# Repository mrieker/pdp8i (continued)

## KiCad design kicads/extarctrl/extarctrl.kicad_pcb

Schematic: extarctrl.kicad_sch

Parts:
C11, C12, C13, C14, C21, C22, C23, C24, C25, C26, C31, C32, C33, C34, C35, C36, C41, C42, C43, C44, C45, C46, C51, C52, C53, C54, C55, C61, C62, C63, C64, C65, C71, C72, C73, C74, C75, C81, C82, C83, C84: C; R_Axial_DIN0207_L6.3mm_D2.5mm_P7.62mm_Horizontal
E11, E21, E31, E41, E51, E71, E81: 74AHC540; DIP-20_W7.62mm
E12, E61: 74AC10
E13: 74AHC86; DIP-14_W7.62mm
E14, E23, E25, E26, E36, E44, E46, E53, E54, E63, E83: 74AHC00; DIP-14_W7.62mm
E22, E32, E42: 74HC85; DIP-16_W7.62mm
E24, E43, E55: 74HC27; DIP-14_W7.62mm
E33, E52, E75: 74HC175; DIP-16_W7.62mm
E34: 74HC30
E35: 74AHC02; DIP-14_W7.62mm
E45, E74: 74AC10; DIP-14_W7.62mm
E62: 74AC11; DIP-14_W7.62mm
E64, E72: 74AHC04; DIP-14_W7.62mm
E65: 74HC30; DIP-14_W7.62mm
E73: 74AHC74; DIP-14_W7.62mm
E82: 74AHC08; DIP-14_W7.62mm
E84: 74AC20; DIP-14_W7.62mm
J1, J2, J3, J4: Conn_01x36; PinHeader_1x36_P2.54mm_Vertical
J5: Conn_02x05_Odd_Even; PinHeader_2x05_P2.54mm_Vertical
R1: 47K; R_Axial_DIN0207_L6.3mm_D2.5mm_P7.62mm_Horizontal

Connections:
/CONSCK: J4.35
/CONSDA: J4.34
/_ACCLEAR: J3.28
/_ACUM_0: J3.7
/_ACUM_1: J2.34
/_ACUM_2: J2.27
/_ACUM_3: J2.20
/_ACUM_4: J2.13
/_ACUM_5: J2.7
/_ACUM_6: J1.35
/_ACUM_7: J1.29
/_ACUM_8: J1.23
/_ACUM_9: J1.16
/_ACUM_10: J1.9
/_ACUM_11: J1.2
/_BRKCYC: J4.33
/_BRKRQST: J3.29
/_BRKWRM: J4.11
/_BUSINI: E71.2 (A0), J3.31
/_BWCOV: J3.32
/_CAINC: J4.12
/_CLOCK: E71.3 (A1), J4.6
/_CYCLE3: J4.13
/_INBUS_0: E51.7 (A5), J3.10
/_INBUS_1: E51.3 (A1), J3.3
/_INBUS_2: E41.7 (A5), J2.30
/_INBUS_3: E41.3 (A1), J2.23
/_INBUS_4: E31.7 (A5), J2.16
/_INBUS_5: E31.4 (A2), J2.10
/_INBUS_6: E21.9 (A7), J2.4
/_INBUS_7: J1.32
/_INBUS_8: E21.4 (A2), J1.26
/_INBUS_9: E11.9 (A7), J1.19
/_INBUS_10: E11.6 (A4), J1.12
/_INBUS_11: E11.3 (A1), J1.5
/_INTINH: J4.15
/_INTRQST: J4.16
/_ION: J3.30
/_IOP: J4.8
/_IOSKIP: J4.17
/_IREG_9: J1.22
/_IREG_10: J1.15
/_IREG_11: J1.8
/_LINK: J4.9
/_LNKTOG: J4.18
/_MAJST_0: E71.8 (A6), J4.22
/_MAJST_1: E71.7 (A5), J4.21
/_MAJST_2: E71.6 (A4), J4.20
/_MAJST_3: E71.5 (A3), J4.19
/_MBUF_0: E51.6 (A4), J3.9
/_MBUF_1: E51.2 (A0), J3.2
/_MBUF_2: E41.6 (A4), J2.29
/_MBUF_3: E41.2 (A0), J2.22
/_MBUF_4: E31.6 (A4), J2.15
/_MBUF_5: E31.3 (A1), J2.9
/_MBUF_6: E21.8 (A6), J2.3
/_MBUF_7: E21.6 (A4), J1.31
/_MBUF_8: E21.3 (A1), J1.25
/_MBUF_9: E11.8 (A6), J1.18
/_MBUF_10: E11.5 (A3), J1.11
/_MBUF_11: E11.2 (A0), J1.4
/_MQUO_0: E51.8 (A6), J3.11
/_MQUO_1: E51.4 (A2), J3.4
/_MQUO_2: E41.8 (A6), J2.31
/_MQUO_3: E41.4 (A2), J2.24
/_MQUO_4: E31.8 (A6), J2.17
/_MQUO_5: E31.5 (A3), J2.11
/_MQUO_6: E31.2 (A0), J2.5
/_MQUO_7: E21.7 (A5), J1.33
/_MQUO_8: E21.5 (A3), J1.27
/_MQUO_9: E21.2 (A0), J1.20
/_MQUO_10: E11.7 (A5), J1.13
/_MQUO_11: E11.4 (A2), J1.6
/_PAUSE: E71.16 (Y2), J4.14
/_RESET: J4.7
/_RUN: J4.10
/_SCTR_0: E51.9 (A7), J3.13
/_SCTR_1: E51.5 (A3), J3.6
/_SCTR_2: E41.9 (A7), J2.33
/_SCTR_3: E41.5 (A3), J2.26
/_SCTR_4: E31.9 (A7), J2.19
/_SWCONT: J4.2
/_SWDEPOS: J3.35
/_SWEXAM: J3.34
/_SWLDAD: J3.33
/_SWSINST: J4.5
/_SWSSTEP: J4.4
/_SWSTART: J4.3
/_TP1: E81.3 (A1), J4.27
/_TP2: E71.9 (A7), J4.28
/_TP3: J4.29
/_TP4: J4.30
/_TS1: J4.23
/_TS2: J4.24
/_TS3: E81.2 (A0), J4.25
/_TS4: J4.26
/_dviover: E73.5 (Q), E74.4
/_extar: E33.11 (~Q2)
/_extarex: E64.9, E65.8
/_extop_1: E52.3 (~Q0), E61.5, E62.13, E63.13, J3.21
/_extop_2: E52.6 (~Q1), E62.2, E63.12, J3.20
/_extop_3: E35.6, E52.11 (~Q2), E61.4, E61.13, J3.19
/_extop_4: E14.4, E14.12, E25.4, E25.10, E26.5, E36.1, E46.2, E46.4, E46.10, E46.12, E52.14 (~Q3), E53.2, E53.4
/_extop_5: E33.3 (~Q0)
/_extop_6: E33.6 (~Q1)
/_extop_dvi: E61.12, E72.13, J3.23
/_extop_muy: E61.6, E72.3, J3.22
/_majst_1: E63.9, E64.4
/_majst_2: E64.10, E65.5
/_majst_3: E64.12, E65.3
/_nmidone: E82.11, E83.5
/_s3clk: E74.13, E75.15 (Q3), J3.24, J5.9
/busini: E71.18 (Y0), E72.1
/clk2: E74.12, E75.4 (D0), J5.2
/clk4: E75.2 (Q0), E75.5 (D1), J5.4
/clk6: E75.7 (Q1), E75.12 (D2), J5.6
/clk8: E75.10 (Q2), J5.8
/clkp1: E63.5, J5.10, R1.1
/clksel: E75.13 (D3), J5.1, J5.3, J5.5, J5.7
/clock: E71.17 (Y1), E73.11 (C), E75.9 (Cp)
/countedshift: E35.4, E83.12
/dviover: E73.6 (~Q), J3.25
/extar: E33.10 (Q2), E65.1
/extarex: E62.11, E64.8, J3.26
/extop_1: E35.9, E52.2 (Q0), E61.1, J3.18
/extop_2: E35.8, E52.7 (Q1), E61.2, E61.3, J3.17
/extop_3: E52.10 (Q2), E62.1, J3.16
/extop_4: E52.15 (Q3), J3.15
/extop_5: E23.5, E33.2 (Q0), E44.5, E44.10, E54.4, E63.1
/extop_6: E14.10, E23.12, E25.1, E26.2, E26.9, E33.7 (Q1), E36.12, E44.1, E44.13, E53.12, E54.2, E54.10, E54.12
/extop_dvi: E72.12, E74.3
/extop_muy: E72.4, E83.1
/extop_nmi: E62.12, E83.4
/inbus_0: E23.9, E51.13 (Y5)
/inbus_1: E51.17 (Y1), E52.4 (D0)
/inbus_2: E41.13 (Y5), E52.5 (D1)
/inbus_3: E41.17 (Y1), E52.12 (D2)
/inbus_4: E31.13 (Y5), E52.13 (D3)
/inbus_5: E31.16 (Y2), E33.4 (D0)
/inbus_6: E21.11 (Y7), E33.5 (D1)
/inbus_8: E21.16 (Y2), E23.10
/inbus_9: E11.11 (Y7), E12.5
/inbus_10: E11.14 (Y4), E12.4
/inbus_11: E11.17 (Y1), E12.3
/majst_0: E62.4, E65.4, E71.12 (Y6)
/majst_000x: E55.6, E62.3, J3.27
/majst_1: E55.3, E64.3, E71.13 (Y5)
/majst_2: E55.5, E64.11, E71.14 (Y4)
/majst_3: E55.4, E64.13, E71.15 (Y3)
/memop: E63.10, E63.11
/mquo_0: E51.12 (Y6), E54.9, E55.13
/mquo_1: E51.16 (Y2), E54.13, E55.2
/mquo_2: E41.12 (Y6), E54.1, E55.1
/mquo_3: E41.16 (Y2), E43.4, E44.12
/mquo_4: E31.12 (Y6), E43.3, E44.2
/mquo_5: E31.15 (Y3), E43.5, E53.13
/mquo_6: E24.10, E26.10, E31.18 (Y0)
/mquo_7: E21.13 (Y5), E24.9, E36.13
/mquo_8: E21.15 (Y3), E24.11, E26.1
/mquo_9: E21.18 (Y0), E24.13, E25.2
/mquo_10: E11.13 (Y5), E23.13, E24.2
/mquo_11: E11.16 (Y2), E14.9, E24.1
/myac_0: E43.9, E53.5, J3.12
/myac_1: E43.10, E46.9, J3.5
/myac_2: E25.5, E43.11, J2.32
/myac_3: E43.1, E46.5, J2.25
/myac_4: E43.13, E46.1, J2.18
/myac_5: E43.2, E53.1, J2.12
/myac_6: E35.12, E36.2, J2.6
/myac_7: E35.11, E46.13, J1.34
/myac_8: E26.4, E35.3, J1.28
/myac_9: E25.9, E35.2, J1.21
/myac_10: E13.9, E14.5, J1.14
/myac_11: E13.10, E14.13, J1.7
/myacstep2_0: E42.10 (A0), E61.8, J3.8
/myacstep2_1: E42.12 (A1), E45.8, J2.35
/myacstep2_2: E12.8, E42.13 (A2), J2.28
/myacstep2_3: E42.15 (A3), E45.6, J2.21
/myacstep2_4: E32.10 (A0), E45.12, J2.14
/myacstep2_5: E32.12 (A1), E53.8, J2.8
/myacstep2_6: E32.13 (A2), E36.6, J2.2
/myacstep2_7: E32.15 (A3), E36.8, J1.30
/myacstep2_8: E22.10 (A0), E26.11, J1.24
/myacstep2_9: E22.12 (A1), E25.11, J1.17
/myacstep2_10: E22.13 (A2), E23.3, J1.10
/myacstep2_11: E14.3, E22.15 (A3), J1.3
/pause: E62.8, E63.4, E71.4 (A2), E74.1
/s3clk: E75.14 (~Q3)
/sctr_0: E51.11 (Y7), E63.2
/sctr_1: E51.15 (Y3), E54.5
/sctr_2: E23.4, E41.11 (Y7)
/sctr_3: E41.15 (Y3), E44.9
/sctr_4: E31.11 (Y7), E44.4
/sctr_5: E74.5, E83.2, E83.13, J3.14
/tp1: E62.5, E81.17 (Y1)
/tp2: E71.11 (Y7), E73.3 (C)
/ts3: E62.9, E81.18 (Y0)
/yreg_0: E42.9 (B0), E51.14 (Y4)
/yreg_1: E42.11 (B1), E51.18 (Y0)
/yreg_2: E41.14 (Y4), E42.14 (B2)
/yreg_3: E41.18 (Y0), E42.1 (B3)
/yreg_4: E31.14 (Y4), E32.9 (B0)
/yreg_5: E31.17 (Y1), E32.11 (B1)
/yreg_6: E21.12 (Y6), E32.14 (B2)
/yreg_7: E21.14 (Y4), E32.1 (B3)
/yreg_8: E21.17 (Y1), E22.9 (B0)
/yreg_9: E11.12 (Y6), E22.11 (B1)
/yreg_10: E11.15 (Y3), E22.14 (B2)
/yreg_11: E11.18 (Y0), E22.1 (B3)
GND: C11.2, C12.2, C13.2, C14.2, C21.2, C22.2, C23.2, C24.2, C25.2, C26.2, C31.2, C32.2, C33.2, C34.2, C35.2, C36.2, C41.2, C42.2, C43.2, C44.2, C45.2, C46.2, C51.2, C52.2, C53.2, C54.2, C55.2, C61.2, C62.2, C63.2, C64.2, C65.2, C71.2, C72.2, C73.2, C74.2, C75.2, C81.2, C82.2, C83.2, C84.2, E11.1 (G1), E11.10 (GND), E11.19 (G2), E12.1, E12.2, E12.7 (GND), E12.13, E13.1, E13.2, E13.4, E13.5, E13.7 (GND), E13.12, E13.13, E14.7 (GND), E21.1 (G1), E21.10 (GND), E21.19 (G2), E22.8 (GND), E23.7 (GND), E24.4, E24.7 (GND), E25.7 (GND), E26.7 (GND), E31.1 (G1), E31.10 (GND), E31.19 (G2), E32.8 (GND), E33.8 (GND), E33.13 (D3), E34.7 (GND), E35.7 (GND), E36.7 (GND), E41.1 (G1), E41.10 (GND), E41.19 (G2), E42.2 (Ia<b), E42.4 (Ia>b), E42.8 (GND), E43.7 (GND), E44.7 (GND), E45.7 (GND), E46.7 (GND), E51.1 (G1), E51.10 (GND), E51.19 (G2), E52.8 (GND), E53.7 (GND), E54.7 (GND), E55.7 (GND), E55.9, E55.10, E55.11, E61.7 (GND), E62.7 (GND), E63.7 (GND), E64.1, E64.5, E64.7 (GND), E65.7 (GND), E71.1 (G1), E71.10 (GND), E71.19 (G2), E72.5, E72.7 (GND), E72.9, E73.7 (GND), E74.7 (GND), E74.9, E74.10, E74.11, E75.8 (GND), E81.1 (G1), E81.4 (A2), E81.5 (A3), E81.6 (A4), E81.7 (A5), E81.8 (A6), E81.9 (A7), E81.10 (GND), E81.19 (G2), E82.1, E82.2, E82.4, E82.5, E82.7 (GND), E82.9, E82.10, E83.7 (GND), E83.9, E83.10, E84.7 (GND), E84.9, E84.10, E84.12, E84.13, J1.36, J2.36, J3.36, J4.36
unnamed: E34.5, E55.12
unnamed: E13.8, E72.11
unnamed: E26.8, E36.5
unnamed: E26.6, E26.12
unnamed: E26.3, E26.13
unnamed: E72.10, E82.13
unnamed: E36.3, E36.4
unnamed: E36.10, E36.11
unnamed: E63.6, E73.12 (D)
unnamed: E73.8 (~Q), E74.2
unnamed: E14.1, E14.11
unnamed: E14.2, E14.8
unnamed: E14.6, E23.1
unnamed: E12.11, E25.6
unnamed: E25.8, E25.12
unnamed: E25.3, E25.13
unnamed: E12.9, E54.3
unnamed: E45.10, E54.6
unnamed: E54.8, E61.10
unnamed: E45.9, E54.11
unnamed: E12.10, E23.6
unnamed: E23.8, E24.5
unnamed: E23.2, E23.11
unnamed: E61.9, E63.3
unnamed: E63.8, E65.6
unnamed: E74.6, E84.1
unnamed: E83.3, E84.2
unnamed: E83.11, E84.4
unnamed: E83.6, E84.5
unnamed: E62.10, E84.6
unnamed: E53.3, E53.9
unnamed: E53.6, E61.11
unnamed: E53.10, E53.11
unnamed: E33.9 (Cp), E52.9 (Cp), E62.6
unnamed: E24.6, E33.12 (D2)
unnamed: E33.1 (~Mr), E52.1 (~Mr), E72.2
unnamed: E12.6, E24.3
unnamed: E34.12, E35.1
unnamed: E35.5, E35.10
unnamed: E34.11, E35.13
unnamed: E45.13, E46.3
unnamed: E45.4, E46.6
unnamed: E45.11, E46.8
unnamed: E36.9, E46.11
unnamed: E24.8, E34.2
unnamed: E24.12, E34.1
unnamed: E34.3, E43.6
unnamed: E34.6, E43.8
unnamed: E34.4, E43.12
unnamed: E44.3, E45.1
unnamed: E44.6, E45.2
unnamed: E44.11, E45.3
unnamed: E44.8, E45.5
unnamed: E34.8, E82.12
unnamed: E32.2 (Ia<b), E42.7 (Oa<b)
unnamed: E32.3 (Ia=b), E42.6 (Oa=b)
unnamed: E32.4 (Ia>b), E42.5 (Oa>b)
unnamed: E22.2 (Ia<b), E32.7 (Oa<b)
unnamed: E22.3 (Ia=b), E32.6 (Oa=b)
unnamed: E22.4 (Ia>b), E32.5 (Oa>b)
unnamed: E22.7 (Oa<b), E73.2 (D)
VCC: C11.1, C12.1, C13.1, C14.1, C21.1, C22.1, C23.1, C24.1, C25.1, C26.1, C31.1, C32.1, C33.1, C34.1, C35.1, C36.1, C41.1, C42.1, C43.1, C44.1, C45.1, C46.1, C51.1, C52.1, C53.1, C54.1, C55.1, C61.1, C62.1, C63.1, C64.1, C65.1, C71.1, C72.1, C73.1, C74.1, C75.1, C81.1, C82.1, C83.1, C84.1, E11.20 (VCC), E12.14 (VCC), E13.14 (VCC), E14.14 (VCC), E21.20 (VCC), E22.16 (VCC), E23.14 (VCC), E24.14 (VCC), E25.14 (VCC), E26.14 (VCC), E31.20 (VCC), E32.16 (VCC), E33.16 (VCC), E34.14 (VCC), E35.14 (VCC), E36.14 (VCC), E41.20 (VCC), E42.3 (Ia=b), E42.16 (VCC), E43.14 (VCC), E44.14 (VCC), E45.14 (VCC), E46.14 (VCC), E51.20 (VCC), E52.16 (VCC), E53.14 (VCC), E54.14 (VCC), E55.14 (VCC), E61.14 (VCC), E62.14 (VCC), E63.14 (VCC), E64.14 (VCC), E65.2, E65.11, E65.12, E65.14 (VCC), E71.20 (VCC), E72.14 (VCC), E73.1 (~R), E73.4 (~S), E73.10 (~S), E73.13 (~R), E73.14 (VCC), E74.14 (VCC), E75.1 (~Mr), E75.16 (VCC), E81.20 (VCC), E82.14 (VCC), E83.14 (VCC), E84.14 (VCC), J1.1, J2.1, J3.1, J4.1, R1.2

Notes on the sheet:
doing execute cycle of extended arithmetic * in FETCH cycle if no memory operand * in EXEC cycle if has memory operand
dviover clocked at every TP2 but we only care about the one during EXEC cycle of DVI it must be valid in time to block the PAUSE during TS3 myacstep2 was valid since just after FETCH TP1 yreg (really MBUF) valid since just after EXEC TP1 ...so it has 3 clocks to soak through the comparators
pause processor at beginning of TS3 while doing step 3 resume when termination condition met
perform step 3 clocking while processor pausing at beginning of TS3 shift registers (AC,MQ) clock on posedge s3clk J5 jumper (@ CLOCK 10MHz): 1-2 : 100nS on; 100nS off (MUY 6.5uS) 3-4 : 200nS on; 200nS off (MUY 8.8uS) 5-6 : 300nS on; 300nS off (MUY 11.1uS) 7-8 : 400nS on; 400nS off (MUY 13.4uS) 9-1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
SHL,ASR,LSR
opcode clocked at TP1 during FETCH * extar = it is an extended arith opcode * memop = the opcode has memory operand
myacstep2 = value to clock into MYAC at TP2 for non-memory ops (NOP,NMI), clocked at FETCH TP2 for memory ops (SCL,MUY,DVI,SHL,ASR,LSR), clocked at EXEC TP2 'or' of the following: extop<4> = 0 : MYAC (ACUM from step 1) extop<5> = 1 : SCTR from prior instruction extop<6> = 1 : MQUO from prior instru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
has memory operand SCL,MUY,DVI,SHL,ASR,LSR
dviover = (myac >= yreg)

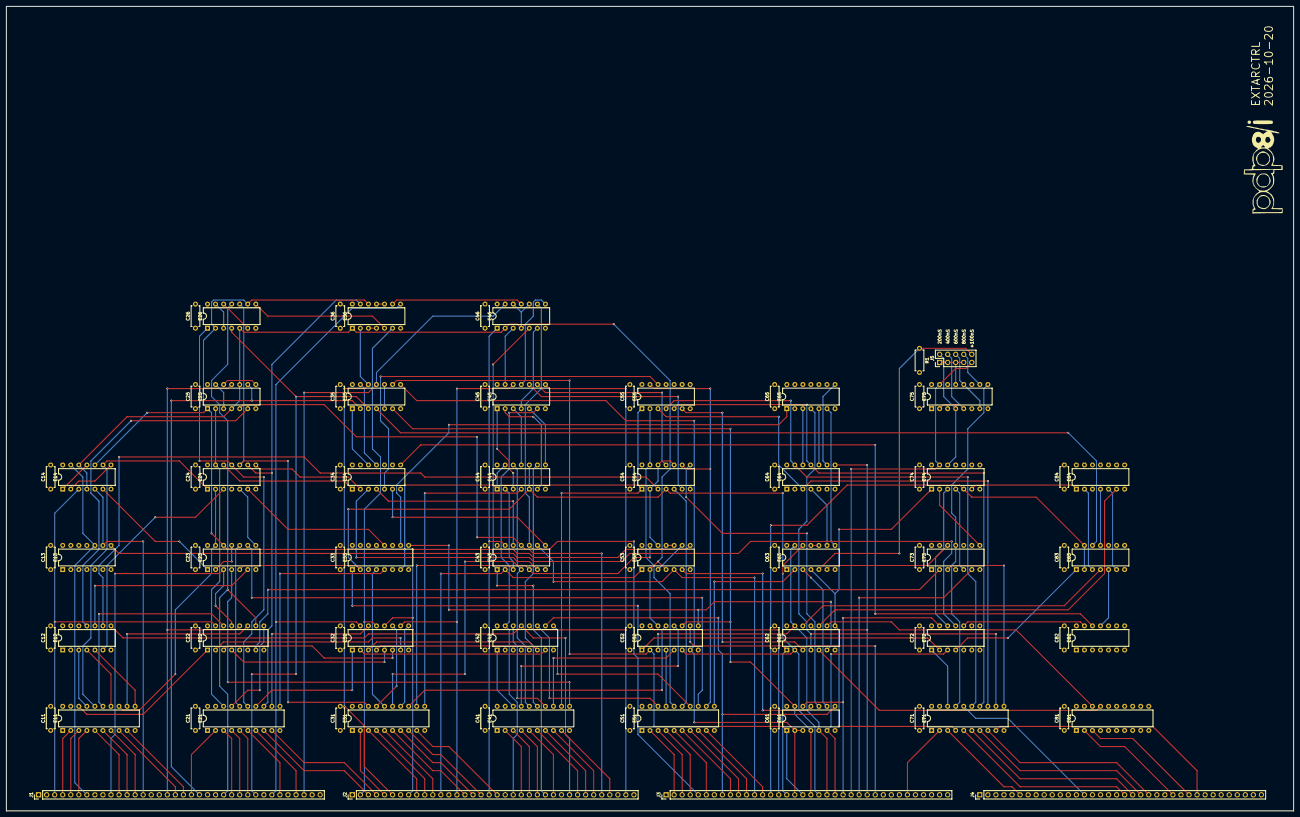
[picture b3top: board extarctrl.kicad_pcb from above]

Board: 4 copper layers, 406.4 x 254.0 mm, 88 parts (0 on the bottom side), 222 nets.

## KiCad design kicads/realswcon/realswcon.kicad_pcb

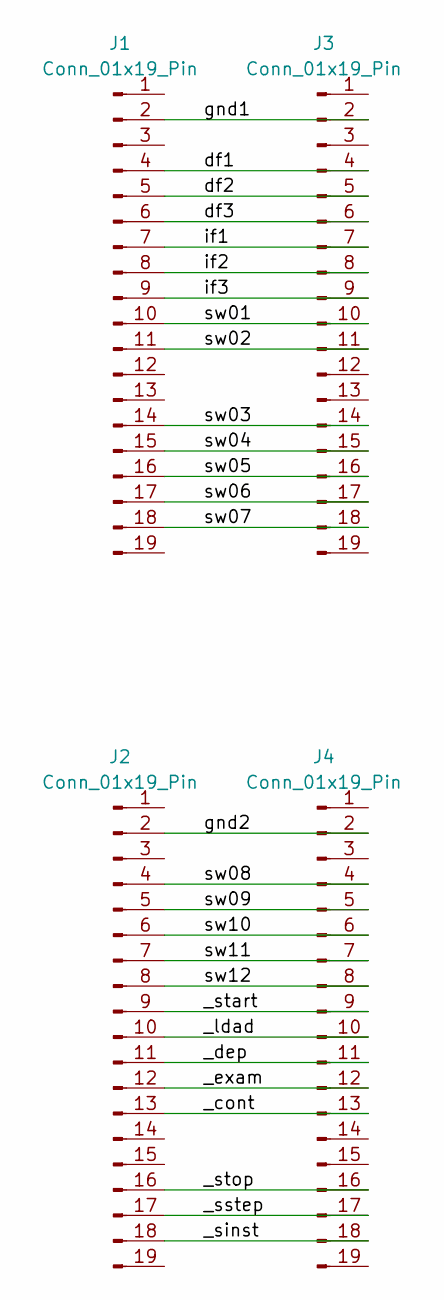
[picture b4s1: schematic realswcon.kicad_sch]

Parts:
J1, J2, J3, J4: Conn_01x19_Pin; PinHeader_1x19_P2.54mm_Vertical

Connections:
/_cont: J2.13, J4.13
/_dep: J2.11, J4.11
/_exam: J2.12, J4.12
/_ldad: J2.10, J4.10
/_sinst: J2.18, J4.18
/_sstep: J2.17, J4.17
/_start: J2.9, J4.9
/_stop: J2.16, J4.16
/df1: J1.4, J3.4
/df2: J1.5, J3.5
/df3: J1.6, J3.6
/gnd1: J1.2, J3.2
/gnd2: J2.2, J4.2
/if1: J1.7, J3.7
/if2: J1.8, J3.8
/if3: J1.9, J3.9
/sw01: J1.10, J3.10
/sw02: J1.11, J3.11
/sw03: J1.14, J3.14
/sw04: J1.15, J3.15
/sw05: J1.16, J3.16
/sw06: J1.17, J3.17
/sw07: J1.18, J3.18
/sw08: J2.4, J4.4
/sw09: J2.5, J4.5
/sw10: J2.6, J4.6
/sw11: J2.7, J4.7
/sw12: J2.8, J4.8

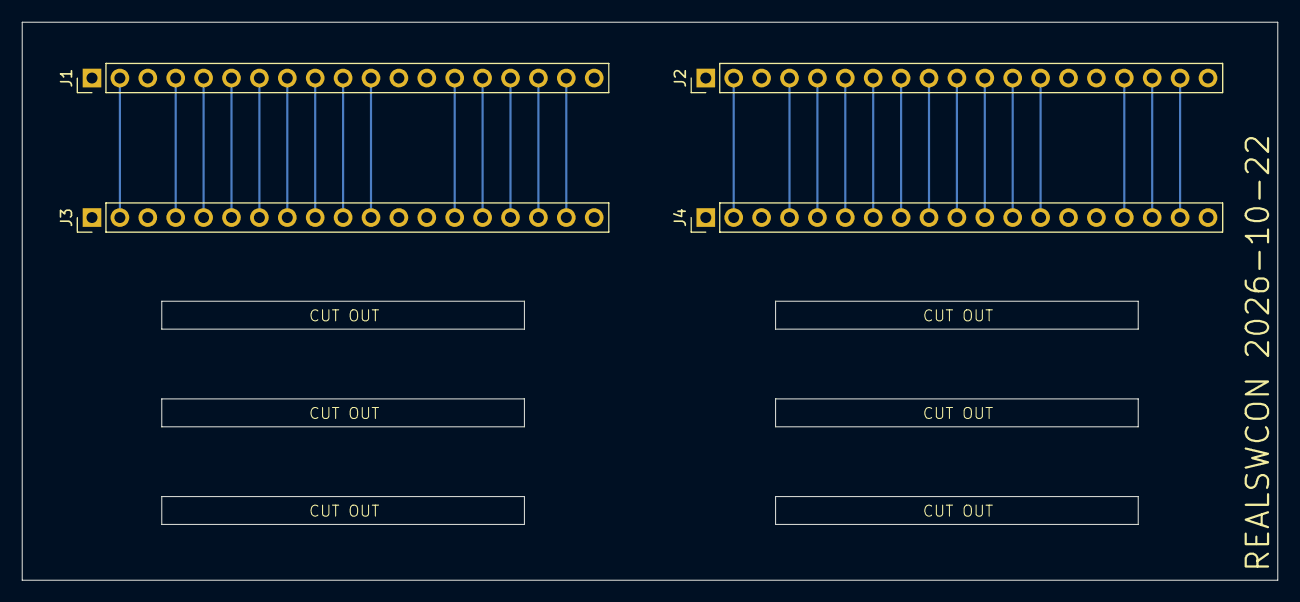
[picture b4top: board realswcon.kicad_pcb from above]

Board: 2 copper layers, 114.3 x 50.8 mm, 4 parts (0 on the bottom side), 28 nets.

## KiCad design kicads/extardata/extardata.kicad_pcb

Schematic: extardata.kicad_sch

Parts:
C11, C12, C13, C14, C15, C16, C17, C18, C21, C22, C23, C24, C25, C26, C27, C28, C31, C32, C33, C34, C35, C36, C37, C38, C41, C42, C43, C44, C45, C46, C47, C48, C51, C52, C53, C54, C55, C56, C57, C58, C61, C62, C63, C64, C65, C66, C67, C68, C71, C72, C73, C74, C75, C76, C77, C78, C81, C82, C83, C84, C85, C86, C87, C88: C; R_Axial_DIN0207_L6.3mm_D2.5mm_P7.62mm_Horizontal
E11, E21, E22, E31, E41, E51, E61, E81, E82: 74AHC540; DIP-20_W7.62mm
E12, E13, E17, E23, E24, E25, E27, E28, E33, E34, E35, E36, E37, E38, E42, E45, E48, E52, E56, E57, E58, E62, E63, E64, E65: 74AC151; DIP-16_W7.62mm
E14, E16, E32, E44, E53, E54: 74AC283; DIP-16_W7.62mm
E15, E43, E83: 74AHC04; DIP-14_W7.62mm
E18: 74AHC32; DIP-14_W7.62mm
E26, E46, E47, E55: 74AHC174; DIP-16_W7.62mm
E66, E68: 74AHC02; DIP-14_W7.62mm
E67: 74HC27; DIP-14_W7.62mm
E71, E72: 74AC161; DIP-16_W7.62mm
E73, E85: 74AHC157; DIP-16_W7.62mm
E74, E76, E77: 74AHC00; DIP-14_W7.62mm
E75, E78, E84: 74AC10; DIP-14_W7.62mm
E86: 74AC11; DIP-14_W7.62mm
E87: 74AHC08; DIP-14_W7.62mm
E88: 74AHC74; DIP-14_W7.62mm
J1, J2, J3, J4: Conn_01x36; PinHeader_1x36_P2.54mm_Vertical

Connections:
/CONSCK: J4.35
/CONSDA: J4.34
/_ACCLEAR: E41.14 (Y4), J3.28
/_ACUM_0: E61.8 (A6), J3.7
/_ACUM_1: E61.4 (A2), J2.34
/_ACUM_2: E51.8 (A6), J2.27
/_ACUM_3: E51.4 (A2), J2.20
/_ACUM_4: E31.8 (A6), J2.13
/_ACUM_5: E31.5 (A3), J2.7
/_ACUM_6: E31.2 (A0), J1.35
/_ACUM_7: E22.6 (A4), J1.29
/_ACUM_8: E22.3 (A1), J1.23
/_ACUM_9: E11.8 (A6), J1.16
/_ACUM_10: E11.5 (A3), J1.9
/_ACUM_11: E11.2 (A0), J1.2
/_BRKCYC: J4.33
/_BRKRQST: J3.29
/_BRKWRM: J4.11
/_BUSINI: E82.4 (A2), J3.31
/_BWCOV: J3.32
/_CAINC: J4.12
/_CLOCK: J4.6
/_CYCLE3: J4.13
/_INBUS_0: E41.15 (Y3), J3.10
/_INBUS_1: E41.16 (Y2), J3.3
/_INBUS_2: E41.17 (Y1), J2.30
/_INBUS_3: E41.18 (Y0), J2.23
/_INBUS_4: E21.11 (Y7), J2.16
/_INBUS_5: E21.12 (Y6), J2.10
/_INBUS_6: E21.13 (Y5), J2.4
/_INBUS_7: E21.14 (Y4), E22.8 (A6), J1.32
/_INBUS_8: E21.15 (Y3), J1.26
/_INBUS_9: E21.16 (Y2), J1.19
/_INBUS_10: E21.17 (Y1), J1.12
/_INBUS_11: E21.18 (Y0), J1.5
/_INTINH: J4.15
/_INTRQST: J4.16
/_ION: J3.30
/_IOP: J4.8
/_IOSKIP: E41.13 (Y5), J4.17
/_IREG_9: J1.22
/_IREG_10: J1.15
/_IREG_11: J1.8
/_LINK: E82.5 (A3), J4.9
/_LNKTOG: E41.11 (Y7), J4.18
/_MAJST_0: E82.6 (A4), J4.22
/_MAJST_1: J4.21
/_MAJST_2: J4.20
/_MAJST_3: J4.19
/_MBUF_0: E61.9 (A7), J3.9
/_MBUF_1: E61.5 (A3), J3.2
/_MBUF_2: E51.9 (A7), J2.29
/_MBUF_3: E51.5 (A3), J2.22
/_MBUF_4: E31.9 (A7), J2.15
/_MBUF_5: E31.6 (A4), J2.9
/_MBUF_6: E31.3 (A1), J2.3
/_MBUF_7: E22.7 (A5), J1.31
/_MBUF_8: E22.4 (A2), J1.25
/_MBUF_9: E11.9 (A7), J1.18
/_MBUF_10: E11.6 (A4), J1.11
/_MBUF_11: E11.3 (A1), J1.4
/_MQUO_0: E82.18 (Y0), J3.11
/_MQUO_1: E61.14 (Y4), J3.4
/_MQUO_2: E61.18 (Y0), J2.31
/_MQUO_3: E51.14 (Y4), J2.24
/_MQUO_4: E51.18 (Y0), J2.17
/_MQUO_5: E31.13 (Y5), J2.11
/_MQUO_6: E31.16 (Y2), J2.5
/_MQUO_7: E22.11 (Y7), J1.33
/_MQUO_8: E22.15 (Y3), J1.27
/_MQUO_9: E22.18 (Y0), J1.20
/_MQUO_10: E11.13 (Y5), J1.13
/_MQUO_11: E11.16 (Y2), J1.6
/_PAUSE: J4.14
/_RESET: J4.7
/_RUN: J4.10
/_SCTR_0: E82.17 (Y1), J3.13
/_SCTR_1: E61.13 (Y5), J3.6
/_SCTR_2: E61.17 (Y1), J2.33
/_SCTR_3: E51.13 (Y5), J2.26
/_SCTR_4: E51.17 (Y1), J2.19
/_SWCONT: J4.2
/_SWDEPOS: J3.35
/_SWEXAM: J3.34
/_SWLDAD: J3.33
/_SWSINST: J4.5
/_SWSSTEP: J4.4
/_SWSTART: J4.3
/_TP1: E81.2 (A0), J4.27
/_TP2: E81.3 (A1), J4.28
/_TP3: J4.29
/_TP4: J4.30
/_TS1: E82.7 (A5), J4.23
/_TS2: E82.8 (A6), J4.24
/_TS3: E82.9 (A7), J4.25
/_TS4: J4.26
/_busini: E46.1 (~Mr), E47.1 (~Mr), E71.1 (~MR), E72.1 (~MR), E83.4
/_enouts: E21.19 (G2), E41.19 (G2), E74.11
/_ensctrld: E71.9 (~PE), E72.9 (~PE), E84.8
/_extop_1: E84.2, E86.5, J3.21
/_extop_2: E84.13, E86.4, J3.20
/_extop_3: E74.2, E84.1, J3.19
/_extop_dvi: E68.3, J3.23
/_extop_muy: E66.3, J3.22
/_s3clk: E74.4, E75.11, E76.2, J3.24
/_ts2: E78.5, E78.13, E83.10
/_ts3: E66.6, E66.12, E67.2, E67.9, E76.4, E83.6
/_yreg_0: E54.6 (B1), E73.3 (I1a), E83.2
/_yreg_1: E43.6, E54.2 (B2), E73.6 (I1b)
/_yreg_2: E43.10, E54.15 (B3), E73.10 (I1c)
/_yreg_3: E43.8, E54.11 (B4), E73.13 (I1d)
/_yreg_4: E43.4, E44.6 (B1), E85.3 (I1a)
/_yreg_5: E43.2, E44.2 (B2)
/_yreg_6: E15.6, E44.15 (B3)
/_yreg_7: E43.12, E44.11 (B4)
/_yreg_8: E15.10, E16.6 (B1)
/_yreg_9: E15.2, E16.2 (B2)
/_yreg_10: E15.12, E16.15 (B3)
/_yreg_11: E15.8, E16.11 (B4)
/acclk: E26.9 (Cp), E55.9 (Cp), E75.8, E88.3 (C)
/acmux_0: E55.3 (D0), E63.5 (Z)
/acmux_1: E55.4 (D1), E62.5 (Z)
/acmux_2: E55.6 (D2), E64.5 (Z)
/acmux_3: E52.5 (Z), E55.11 (D3)
/acmux_4: E42.5 (Z), E55.13 (D4)
/acmux_5: E33.5 (Z), E55.14 (D5)
/acmux_6: E23.5 (Z), E26.3 (D0)
/acmux_7: E24.5 (Z), E26.4 (D1)
/acmux_8: E25.5 (Z), E26.6 (D2)
/acmux_9: E13.5 (Z), E26.11 (D3)
/acmux_10: E17.5 (Z), E26.13 (D4)
/acmux_11: E12.5 (Z), E26.14 (D5)
/acsel_0: E12.11 (S0), E13.11 (S0), E17.11 (S0), E23.11 (S0), E24.11 (S0), E25.11 (S0), E33.11 (S0), E42.11 (S0), E52.11 (S0), E62.11 (S0), E63.11 (S0), E64.11 (S0), E78.6
/acsel_1: E12.10 (S1), E13.10 (S1), E17.10 (S1), E23.10 (S1), E24.10 (S1), E25.10 (S1), E33.10 (S1), E42.10 (S1), E52.10 (S1), E62.10 (S1), E63.10 (S1), E64.10 (S1), E67.8
/acsel_2: E12.9 (S2), E13.9 (S2), E17.9 (S2), E23.9 (S2), E24.9 (S2), E25.9 (S2), E33.9 (S2), E42.9 (S2), E52.9 (S2), E62.9 (S2), E63.9 (S2), E64.9 (S2), E66.4
/acsel_zero: E12.7 (~E), E13.7 (~E), E17.7 (~E), E23.7 (~E), E24.7 (~E), E25.7 (~E), E33.7 (~E), E42.7 (~E), E52.7 (~E), E62.7 (~E), E63.7 (~E), E64.7 (~E), E87.3
/acum_0: E61.12 (Y6), E63.4 (I0)
/acum_1: E61.16 (Y2), E62.4 (I0)
/acum_2: E51.12 (Y6), E64.4 (I0)
/acum_3: E51.16 (Y2), E52.4 (I0)
/acum_4: E31.12 (Y6), E42.4 (I0)
/acum_5: E31.15 (Y3), E33.4 (I0)
/acum_6: E23.4 (I0), E31.18 (Y0)
/acum_7: E22.14 (Y4), E24.4 (I0)
/acum_8: E22.17 (Y1), E25.4 (I0)
/acum_9: E11.12 (Y6), E13.4 (I0)
/acum_10: E11.15 (Y3), E17.4 (I0)
/acum_11: E11.18 (Y0), E12.4 (I0)
/busini: E82.16 (Y2), E83.3
/clocksctr: E71.2 (CP), E72.2 (CP), E74.6
/dvi_shl: E67.1, E67.3, E67.10, E68.1
/dviacstep_0: E54.4 (S1), E63.1 (I3)
/dviacstep_1: E54.1 (S2), E62.1 (I3)
/dviacstep_2: E54.13 (S3), E64.1 (I3)
/dviacstep_3: E52.1 (I3), E54.10 (S4)
/dviacstep_4: E42.1 (I3), E44.4 (S1)
/dviacstep_5: E33.1 (I3), E44.1 (S2)
/dviacstep_6: E23.1 (I3), E44.13 (S3)
/dviacstep_7: E24.1 (I3), E44.10 (S4)
/dviacstep_8: E16.4 (S1), E25.1 (I3)
/dviacstep_9: E13.1 (I3), E16.1 (S2)
/dviacstep_10: E16.13 (S3), E17.1 (I3)
/dviacstep_11: E12.1 (I3), E16.10 (S4)
/dvicarry: E16.9 (C23), E18.5
/dviover: E65.1 (I3), J3.25
/dviqbit: E18.6, E37.1 (I3), E68.2
/extarex: E74.10, E74.12, E75.2, E84.10, J3.26
/extop_1: E65.11 (S0), E77.5, J3.18
/extop_2: E65.10 (S1), E66.8, E74.1, J3.17
/extop_3: E65.9 (S2), E67.4, E86.3, J3.16
/extop_4: E75.1, J3.15
/inbus_7: E22.12 (Y6), E87.1
/link: E65.3 (I1), E65.4 (I0), E76.5, E82.15 (Y3)
/majst_0: E82.14 (Y4), E84.5
/majst_000x: E84.3, J3.27
/mqclk: E46.9 (Cp), E47.9 (Cp), E76.3
/mqmux_0: E37.5 (Z), E47.3 (D0)
/mqmux_1: E47.4 (D1), E56.5 (Z)
/mqmux_2: E47.6 (D2), E57.5 (Z)
/mqmux_3: E47.11 (D3), E48.5 (Z)
/mqmux_4: E47.13 (D4), E58.5 (Z)
/mqmux_5: E28.5 (Z), E47.14 (D5)
/mqmux_6: E34.5 (Z), E46.3 (D0)
/mqmux_7: E36.5 (Z), E46.4 (D1)
/mqmux_8: E45.5 (Z), E46.6 (D2)
/mqmux_9: E35.5 (Z), E46.11 (D3)
/mqmux_10: E38.5 (Z), E46.13 (D4)
/mqmux_11: E27.5 (Z), E46.14 (D5)
/mqsel_0: E27.11 (S0), E28.11 (S0), E34.11 (S0), E35.11 (S0), E36.11 (S0), E37.11 (S0), E38.11 (S0), E45.11 (S0), E48.11 (S0), E56.11 (S0), E57.11 (S0), E58.11 (S0), E78.12
/mqsel_1: E27.10 (S1), E28.10 (S1), E34.10 (S1), E35.10 (S1), E36.10 (S1), E37.10 (S1), E38.10 (S1), E45.10 (S1), E48.10 (S1), E56.10 (S1), E57.10 (S1), E58.10 (S1), E67.12
/mqsel_2: E27.9 (S2), E28.9 (S2), E34.9 (S2), E35.9 (S2), E36.9 (S2), E37.9 (S2), E38.9 (S2), E45.9 (S2), E48.9 (S2), E56.9 (S2), E57.9 (S2), E58.9 (S2), E66.13
/mquo_0: E47.2 (Q0), E56.1 (I3), E56.14 (I5), E56.15 (I4), E66.2, E82.2 (A0)
/mquo_1: E37.2 (I2), E37.12 (I7), E37.13 (I6), E47.5 (Q1), E57.1 (I3), E57.14 (I5), E57.15 (I4), E61.6 (A4)
/mquo_2: E47.7 (Q2), E48.1 (I3), E48.14 (I5), E48.15 (I4), E56.2 (I2), E56.12 (I7), E56.13 (I6), E61.2 (A0)
/mquo_3: E47.10 (Q3), E51.6 (A4), E57.2 (I2), E57.12 (I7), E57.13 (I6), E58.1 (I3), E58.14 (I5), E58.15 (I4)
/mquo_4: E28.1 (I3), E28.14 (I5), E28.15 (I4), E47.12 (Q4), E48.2 (I2), E48.12 (I7), E48.13 (I6), E51.2 (A0)
/mquo_5: E31.7 (A5), E34.1 (I3), E34.14 (I5), E34.15 (I4), E47.15 (Q5), E58.2 (I2), E58.12 (I7), E58.13 (I6)
/mquo_6: E28.2 (I2), E28.12 (I7), E28.13 (I6), E31.4 (A2), E36.1 (I3), E36.14 (I5), E36.15 (I4), E46.2 (Q0)
/mquo_7: E22.9 (A7), E34.2 (I2), E34.12 (I7), E34.13 (I6), E45.1 (I3), E45.14 (I5), E45.15 (I4), E46.5 (Q1)
/mquo_8: E22.5 (A3), E35.1 (I3), E35.14 (I5), E35.15 (I4), E36.2 (I2), E36.12 (I7), E36.13 (I6), E46.7 (Q2)
/mquo_9: E22.2 (A0), E38.1 (I3), E38.14 (I5), E38.15 (I4), E45.2 (I2), E45.12 (I7), E45.13 (I6), E46.10 (Q3)
/mquo_10: E11.7 (A5), E27.1 (I3), E27.14 (I5), E27.15 (I4), E35.2 (I2), E35.12 (I7), E35.13 (I6), E46.12 (Q4)
/mquo_11: E11.4 (A2), E38.2 (I2), E38.12 (I7), E38.13 (I6), E46.15 (Q5), E54.5 (A1), E63.14 (I5), E63.15 (I4)
/muy_lsr: E66.1, E66.9, E67.5, E77.1
/muyacstep_0: E53.1 (S2), E63.2 (I2)
/muyacstep_1: E53.13 (S3), E62.2 (I2)
/muyacstep_2: E53.10 (S4), E64.2 (I2)
/muyacstep_3: E32.4 (S1), E52.2 (I2)
/muyacstep_4: E32.1 (S2), E42.2 (I2)
/muyacstep_5: E32.13 (S3), E33.2 (I2)
/muyacstep_6: E23.2 (I2), E32.10 (S4)
/muyacstep_7: E14.4 (S1), E24.2 (I2)
/muyacstep_8: E14.1 (S2), E25.2 (I2)
/muyacstep_9: E13.2 (I2), E14.13 (S3)
/muyacstep_10: E14.10 (S4), E17.2 (I2)
/muyacstep_11: E12.2 (I2), E14.9 (C23)
/muymqstep_11: E27.2 (I2), E53.4 (S1)
/myac_0: E27.12 (I7), E27.13 (I6), E37.3 (I1), E41.5 (A3), E53.5 (A1), E54.3 (A2), E55.2 (Q0), E62.14 (I5), E62.15 (I4), J3.12
/myac_1: E41.4 (A2), E53.3 (A2), E54.14 (A3), E55.5 (Q1), E56.3 (I1), E63.12 (I7), E63.13 (I6), E64.14 (I5), E64.15 (I4), J3.5
/myac_2: E41.3 (A1), E52.14 (I5), E52.15 (I4), E53.14 (A3), E54.12 (A4), E55.7 (Q2), E57.3 (I1), E62.12 (I7), E62.13 (I6), J2.32
/myac_3: E41.2 (A0), E42.14 (I5), E42.15 (I4), E44.5 (A1), E48.3 (I1), E53.12 (A4), E55.10 (Q3), E64.12 (I7), E64.13 (I6), J2.25
/myac_4: E21.9 (A7), E32.5 (A1), E33.14 (I5), E33.15 (I4), E44.3 (A2), E52.12 (I7), E52.13 (I6), E55.12 (Q4), E58.3 (I1), J2.18
/myac_5: E21.8 (A6), E23.14 (I5), E23.15 (I4), E28.3 (I1), E32.3 (A2), E42.12 (I7), E42.13 (I6), E44.14 (A3), E55.15 (Q5), J2.12
/myac_6: E21.7 (A5), E24.14 (I5), E24.15 (I4), E26.2 (Q0), E32.14 (A3), E33.12 (I7), E33.13 (I6), E34.3 (I1), E44.12 (A4), J2.6
/myac_7: E16.5 (A1), E21.6 (A4), E23.12 (I7), E23.13 (I6), E25.14 (I5), E25.15 (I4), E26.5 (Q1), E32.12 (A4), E36.3 (I1), J1.34
/myac_8: E13.14 (I5), E13.15 (I4), E14.5 (A1), E16.3 (A2), E21.5 (A3), E24.12 (I7), E24.13 (I6), E26.7 (Q2), E45.3 (I1), J1.28
/myac_9: E14.3 (A2), E16.14 (A3), E17.14 (I5), E17.15 (I4), E21.4 (A2), E25.12 (I7), E25.13 (I6), E26.10 (Q3), E35.3 (I1), J1.21
/myac_10: E12.14 (I5), E12.15 (I4), E13.12 (I7), E13.13 (I6), E14.14 (A3), E16.12 (A4), E21.3 (A1), E26.12 (Q4), E38.3 (I1), J1.14
/myac_11: E12.13 (I6), E14.12 (A4), E17.12 (I7), E17.13 (I6), E18.4, E21.2 (A0), E26.15 (Q5), E27.3 (I1), E65.13 (I6), E76.13, J1.7
/myacstep2_0: E63.3 (I1), J3.8
/myacstep2_1: E62.3 (I1), J2.35
/myacstep2_2: E64.3 (I1), J2.28
/myacstep2_3: E52.3 (I1), J2.21
/myacstep2_4: E42.3 (I1), J2.14
/myacstep2_5: E33.3 (I1), J2.8
/myacstep2_6: E23.3 (I1), J2.2
/myacstep2_7: E24.3 (I1), J1.30
/myacstep2_8: E25.3 (I1), J1.24
/myacstep2_9: E13.3 (I1), J1.17
/myacstep2_10: E17.3 (I1), J1.10
/myacstep2_11: E12.3 (I1), J1.3
/mylink: E41.9 (A7), E65.5 (Z)
/sctr_0: E72.14 (Q0), E82.3 (A1)
/sctr_1: E61.7 (A5), E72.13 (Q1)
/sctr_2: E61.3 (A1), E72.12 (Q2)
/sctr_3: E51.7 (A5), E72.11 (Q3)
/sctr_4: E51.3 (A1), E71.14 (Q0)
/sctr_5: E71.13 (Q1), J3.14
/shllink: E65.14 (I5), E65.15 (I4), E88.5 (Q)
/tp1: E81.18 (Y0), E84.4
/tp2: E74.9, E75.13, E81.17 (Y1), E83.13
/ts1: E82.13 (Y5), E87.2
/ts2: E82.12 (Y6), E83.11, E84.9
/ts3: E71.7 (CEP), E72.7 (CEP), E72.10 (CET), E74.13, E76.12, E77.2, E77.4, E82.11 (Y7), E83.5
/yreg_0: E53.6 (B1), E61.11 (Y7), E83.1
/yreg_1: E43.5, E53.2 (B2), E61.15 (Y3)
/yreg_2: E43.11, E51.11 (Y7), E53.15 (B3)
/yreg_3: E43.9, E51.15 (Y3), E53.11 (B4)
/yreg_4: E31.11 (Y7), E32.6 (B1), E43.3
/yreg_5: E31.14 (Y4), E32.2 (B2), E43.1
/yreg_6: E15.5, E31.17 (Y1), E32.15 (B3)
/yreg_7: E22.13 (Y5), E32.11 (B4), E43.13
/yreg_8: E14.6 (B1), E15.11, E22.16 (Y2)
/yreg_9: E11.11 (Y7), E14.2 (B2), E15.1
/yreg_10: E11.14 (Y4), E14.15 (B3), E15.13
/yreg_11: E11.17 (Y1), E14.11 (B4), E15.9
GND: C11.2, C12.2, C13.2, C14.2, C15.2, C16.2, C17.2, C18.2, C21.2, C22.2, C23.2, C24.2, C25.2, C26.2, C27.2, C28.2, C31.2, C32.2, C33.2, C34.2, C35.2, C36.2, C37.2, C38.2, C41.2, C42.2, C43.2, C44.2, C45.2, C46.2, C47.2, C48.2, C51.2, C52.2, C53.2, C54.2, C55.2, C56.2, C57.2, C58.2, C61.2, C62.2, C63.2, C64.2, C65.2, C66.2, C67.2, C68.2, C71.2, C72.2, C73.2, C74.2, C75.2, C76.2, C77.2, C78.2, C81.2, C82.2, C83.2, C84.2, C85.2, C86.2, C87.2, C88.2, E11.1 (G1), E11.10 (GND), E11.19 (G2), E12.8 (GND), E12.12 (I7), E13.8 (GND), E14.8 (GND), E15.3, E15.7 (GND), E16.8 (GND), E17.8 (GND), E18.1, E18.2, E18.7 (GND), E18.9, E18.10, E18.12, E18.13, E21.1 (G1), E21.10 (GND), E22.1 (G1), E22.10 (GND), E22.19 (G2), E23.8 (GND), E24.8 (GND), E25.8 (GND), E26.8 (GND), E27.4 (I0), E27.7 (~E), E27.8 (GND), E28.4 (I0), E28.7 (~E), E28.8 (GND), E31.1 (G1), E31.10 (GND), E31.19 (G2), E32.8 (GND), E33.8 (GND), E34.4 (I0), E34.7 (~E), E34.8 (GND), E35.4 (I0), E35.7 (~E), E35.8 (GND), E36.4 (I0), E36.7 (~E), E36.8 (GND), E37.4 (I0), E37.7 (~E), E37.8 (GND), E37.14 (I5), E37.15 (I4), E38.4 (I0), E38.7 (~E), E38.8 (GND), E41.1 (G1), E41.10 (GND), E42.8 (GND), E43.7 (GND), E44.8 (GND), E45.4 (I0), E45.7 (~E), E45.8 (GND), E46.8 (GND), E47.8 (GND), E48.4 (I0), E48.7 (~E), E48.8 (GND), E51.1 (G1), E51.10 (GND), E51.19 (G2), E52.8 (GND), E53.7 (C0), E53.8 (GND), E54.8 (GND), E55.8 (GND), E56.4 (I0), E56.7 (~E), E56.8 (GND), E57.4 (I0), E57.7 (~E), E57.8 (GND), E58.4 (I0), E58.7 (~E), E58.8 (GND), E61.1 (G1), E61.10 (GND), E61.19 (G2), E62.8 (GND), E63.8 (GND), E64.8 (GND), E65.2 (I2), E65.7 (~E), E65.8 (GND), E65.12 (I7), E66.7 (GND), E67.7 (GND), E68.5, E68.6, E68.7 (GND), E68.8, E68.9, E68.11, E68.12, E71.5 (D2), E71.6 (D3), E71.8 (GND), E72.8 (GND), E73.2 (I0a), E73.5 (I0b), E73.8 (GND), E73.14 (I0d), E74.7 (GND), E75.3, E75.4, E75.5, E75.7 (GND), E76.7 (GND), E77.7 (GND), E77.9, E77.10, E77.12, E77.13, E78.7 (GND), E78.9, E78.10, E78.11, E81.1 (G1), E81.4 (A2), E81.5 (A3), E81.6 (A4), E81.7 (A5), E81.8 (A6), E81.9 (A7), E81.10 (GND), E81.19 (G2), E82.1 (G1), E82.10 (GND), E82.19 (G2), E83.7 (GND), E83.9, E84.7 (GND), E85.8 (GND), E85.10 (I1c), E85.11 (I0c), E85.13 (I1d), E85.14 (I0d), E86.1, E86.2, E86.7 (GND), E86.9, E86.10, E86.11, E86.13, E87.4, E87.5, E87.7 (GND), E87.9, E87.10, E87.12, E87.13, E88.7 (GND), E88.10 (~S), E88.11 (C), E88.12 (D), E88.13 (~R), J1.36, J2.36, J3.36, J4.36
unnamed: E74.5, E83.12
unnamed: E71.10 (CET), E72.15 (TC)
unnamed: E73.15 (E), E85.15 (E), E86.6
unnamed: E73.1 (S), E74.3, E85.1 (S)
unnamed: E71.3 (D0), E85.4 (Za)
unnamed: E71.4 (D1), E85.7 (Zb)
unnamed: E72.3 (D0), E73.4 (Za)
unnamed: E72.4 (D1), E73.7 (Zb)
unnamed: E72.5 (D2), E73.9 (Zc)
unnamed: E72.6 (D3), E73.12 (Zd)
unnamed: E76.8, E88.2 (D)
unnamed: E32.7 (C0), E53.9 (C23)
unnamed: E14.7 (C0), E32.9 (C23)
unnamed: E66.5, E66.11, E67.6
unnamed: E66.10, E67.11, E67.13
unnamed: E75.9, E84.6
unnamed: E84.11, E84.12
unnamed: E77.3, E78.1, E78.3
unnamed: E77.6, E78.2, E78.4
unnamed: E74.8, E75.10
unnamed: E75.12, E76.1
unnamed: E76.6, E76.9
unnamed: E76.10, E76.11
unnamed: E44.7 (C0), E54.9 (C23)
unnamed: E16.7 (C0), E44.9 (C23)
VCC: C11.1, C12.1, C13.1, C14.1, C15.1, C16.1, C17.1, C18.1, C21.1, C22.1, C23.1, C24.1, C25.1, C26.1, C27.1, C28.1, C31.1, C32.1, C33.1, C34.1, C35.1, C36.1, C37.1, C38.1, C41.1, C42.1, C43.1, C44.1, C45.1, C46.1, C47.1, C48.1, C51.1, C52.1, C53.1, C54.1, C55.1, C56.1, C57.1, C58.1, C61.1, C62.1, C63.1, C64.1, C65.1, C66.1, C67.1, C68.1, C71.1, C72.1, C73.1, C74.1, C75.1, C76.1, C77.1, C78.1, C81.1, C82.1, C83.1, C84.1, C85.1, C86.1, C87.1, C88.1, E11.20 (VCC), E12.16 (VCC), E13.16 (VCC), E14.16 (VCC), E15.14 (VCC), E16.16 (VCC), E17.16 (VCC), E18.14 (VCC), E21.20 (VCC), E22.20 (VCC), E23.16 (VCC), E24.16 (VCC), E25.16 (VCC), E26.1 (~Mr), E26.16 (VCC), E27.16 (VCC), E28.16 (VCC), E31.20 (VCC), E32.16 (VCC), E33.16 (VCC), E34.16 (VCC), E35.16 (VCC), E36.16 (VCC), E37.16 (VCC), E38.16 (VCC), E41.6 (A4), E41.7 (A5), E41.8 (A6), E41.20 (VCC), E42.16 (VCC), E43.14 (VCC), E44.16 (VCC), E45.16 (VCC), E46.16 (VCC), E47.16 (VCC), E48.16 (VCC), E51.20 (VCC), E52.16 (VCC), E53.16 (VCC), E54.7 (C0), E54.16 (VCC), E55.1 (~Mr), E55.16 (VCC), E56.16 (VCC), E57.16 (VCC), E58.16 (VCC), E61.20 (VCC), E62.16 (VCC), E63.16 (VCC), E64.16 (VCC), E65.16 (VCC), E66.14 (VCC), E67.14 (VCC), E68.14 (VCC), E71.16 (VCC), E72.16 (VCC), E73.11 (I0c), E73.16 (VCC), E74.14 (VCC), E75.14 (VCC), E76.14 (VCC), E77.14 (VCC), E78.14 (VCC), E81.20 (VCC), E82.20 (VCC), E83.14 (VCC), E84.14 (VCC), E85.2 (I0a), E85.5 (I0b), E85.6 (I1b), E85.16 (VCC), E86.14 (VCC), E87.14 (VCC), E88.1 (~R), E88.4 (~S), E88.14 (VCC), J1.1, J2.1, J3.1, J4.1

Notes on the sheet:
multiply step is a shift right when multiplier bit is zero
clock SCTR at TP2 or while step 3 stepping
divide step is a shift left when quotient bit is zero
LINK bit for left shifts: * loaded at TP2 from processor LINK * clocked by s3clk pulses during shifts
acsel condition 0 TS1 & msfetch - get initial ACUM contents into MYAC 1 TS2 & extarex - get step 2 results into ACUM 2 TS3 & (extop31 == 2 & muymbit) - MUY step with multiplier bit set 3 TS3 & (extop31 == 3 & dviqbit) - DVI step with quotient bit set 4 TS3 & (extop31 == 4) - NMI step 5 TS3 & (extop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
load 0 at TP2 for NMI load 20 at TP2 for MUY,DVI load ~YREG at TP2 for SCL,SHL,ASR,LSR
enable incrementing during TS3 (step 3)
memory operand follows opcode retained in MBUF by processor throughout EXEC cycle
TP2 & extarex: load step2 result
s3clk: shift/arith step
TP1 & FETCH: load ACUM or zero
extop<3:1> 0 : NOP : new link = old link 1 : SCL : new link = old link 2 : MUY : new link = 0 3 : DVI : new link = overflow 4 : NMI : new link = last bit shifted out 5 : SHL : new link = last bit shifted out 6 : ASR : new link = sign bit 7 : LSR : new link = 0
clear SCTR on bus init
enable loading during TS2 for extarex cycles and extop<3:1> ne 000

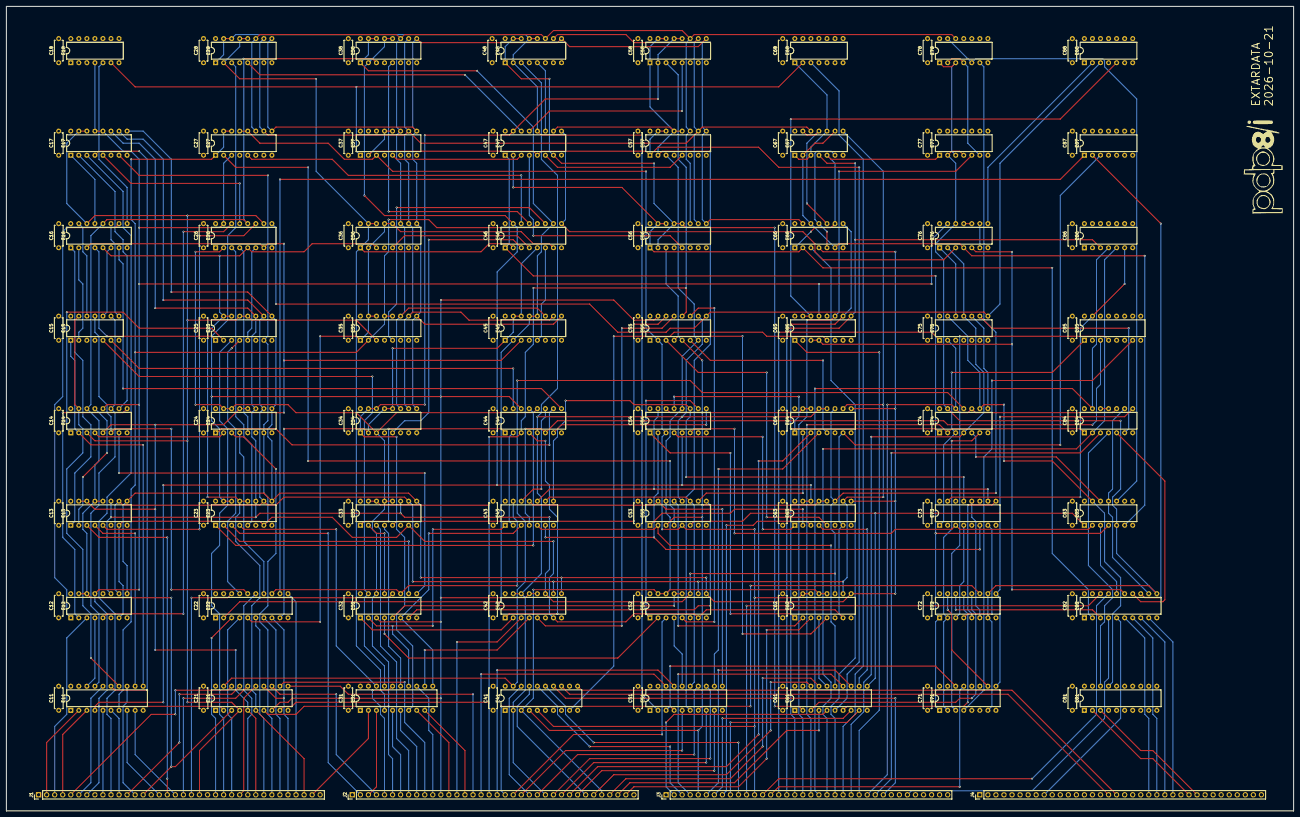
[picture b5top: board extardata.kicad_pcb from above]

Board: 4 copper layers, 406.4 x 254.0 mm, 132 parts (0 on the bottom side), 261 nets.
